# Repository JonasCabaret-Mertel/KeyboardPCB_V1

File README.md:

# KeyboardPCB_V1
My first keyboard PCB following ai03/masterzen guides

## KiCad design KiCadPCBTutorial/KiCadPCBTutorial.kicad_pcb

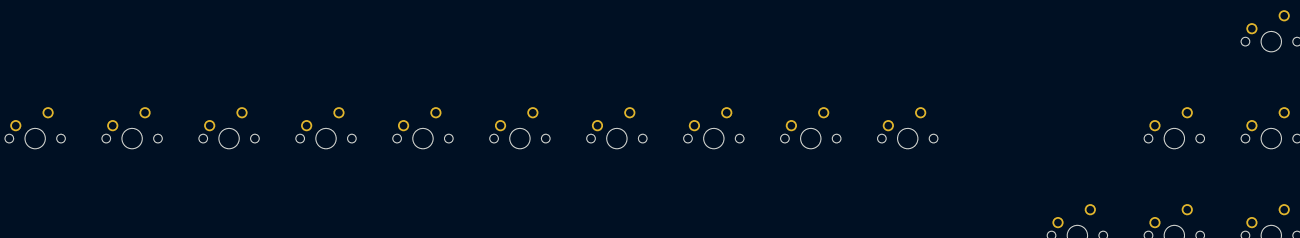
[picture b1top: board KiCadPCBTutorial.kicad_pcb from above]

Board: 2 copper layers, 18 parts (1 on the bottom side), 2 nets, no tracks yet.

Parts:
C4: .1uF; C_0805_2012Metric
K42: '; SW_Cherry_MX_1.00u_PCB
K44, K58: PGUP; SW_Cherry_MX_1.00u_PCB
K46: Z; SW_Cherry_MX_1.00u_PCB
K47: X; SW_Cherry_MX_1.00u_PCB
K48: C; SW_Cherry_MX_1.00u_PCB
K49: V; SW_Cherry_MX_1.00u_PCB
K50: B; SW_Cherry_MX_1.00u_PCB
K51: N; SW_Cherry_MX_1.00u_PCB
K52: M; SW_Cherry_MX_1.00u_PCB
K53: ,<; SW_Cherry_MX_1.00u_PCB
K54: .>; SW_Cherry_MX_1.00u_PCB
K55: /?; SW_Cherry_MX_1.00u_PCB
K57: ARUP; SW_Cherry_MX_1.00u_PCB
K65: ARLEFT; SW_Cherry_MX_1.00u_PCB
K66: ARDWN; SW_Cherry_MX_1.00u_PCB
K67: ARRGHT; SW_Cherry_MX_1.00u_PCB

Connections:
col13: K57.1, K66.1
col14: K44.1, K58.1, K67.1
